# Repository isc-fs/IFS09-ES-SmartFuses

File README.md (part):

# IFS09-ES-SmartFuses

Hardware design, KiCad schematics, PCB layout, multi-rail DC-DC power conversion, and CAN telemetry firmware for the **Smart Fusibles Board** of the **IFS09**, developed for the **ISC Formula Student Racing Team** (Season 2026/2027).

[-green.svg)]()
[-purple.svg)]()
[-red.svg)]()

---

## Getting started

1. Create a GitHub account if you don't have one yet.
2. Download and install [GitHub Desktop](https://desktop.github.com/) (beginner) or [Git CLI](https://git-scm.com/book/en/v2/Getting-Started-Installing-Git) (advanced).
   - If this is your first time using GitHub Desktop, make sure to read the [User Manual](https://help.github.com/desktop/guides/).
   - If this is your first time using Git, start with a tutorial:
     - [Git Tutorial](https://git-scm.com/docs/gittutorial)
     - [Atlassian Git Tutorial](https://www.atlassian.com/git/tutorials/)
   - Keep a copy of [GitHub's Git Cheat Sheet](https://services.github.com/kit/downloads/github-git-cheat-sheet.pdf) handy as a reference.

3. Clone this repository to your machine:
   - **SSH:** `git@github.com:isc-fs/IFS09-ES-SmartFuses.git`
   - **HTTPS:** `https://github.com/isc-fs/IFS09-ES-SmartFuses.git`

---

## How we work with this repository

### Main branches

The repository follows standard ISC branching rules:

* **`main`** is the production branch. It contains only validated hardware releases, schematics, and documentation ready for track operations. Never work directly on it.
* **`dev`** (or active feature branches) is the development and integration point. Never commit directly to `main` — all changes arrive through a reviewed Pull Request.

```
main  ──────────────────●──────────────────────●──▶  (validated releases only)
                        ↑                      ↑
dev   ──────●───●───●───●───●───●───●───●───●──●──▶  (continuous integration)
            ↑   ↑       ↑   ↑   ↑       ↑   ↑
          feat/1 fix/1 feat/2 fix/2   feat/3 fix/3
```

### Feature branches

All work — whether a new hardware revision, firmware update, or bug fix — is done on a **feature branch** created from `dev` (or `main`). When the work is ready, a Pull Request is opened, reviewed, merged, and the branch is deleted.

```
feat/<n>   →  new functionality / hardware addition (feat/1, feat/2, feat/3 ...)
fix/<n>    →  bug fix / schematic correction       (fix/1,  fix/2,  fix/3  ...)
```

### Step-by-step workflow

1. **Create the branch:**
   ```bash
   git checkout main
   git pull origin main
   git checkout -b feat/your-feature-name
   ```
2. **Work and commit:**
   ```bash
   git add .
   git commit -m "feat(hw): add reverse polarity protection to 24V input"
   ```
3. **Push and open Pull Request:**
   ```bash
   git push origin feat/your-feature-name
   ```
   Open a PR against `main` (or `dev`), verify 0 KiCad DRC/ERC errors, provide test evidence, and request review from the Electronics Subsystem Technical Director.

---

## 1. Project Overview & System Purpose

The **IFS09 Smart Fusibles Board** acts as the primary low-voltage (LV) power distribution, multi-rail DC-DC conversion, circuit protection, and digital power telemetry hub for the IFS09 race car.

It evolves the previous passive revision (`PCB_FUSIBLES_XT60` v2) into an active, intelligent subsystem that:
1. Replaces non-locking friction-fit XT-60 connectors with an automotive positive-locking **Molex Mega-Fit** 4-pin header.
2. Protects **12 independent power channels** using **Keystone 3568** automotive mini blade fuse clips with dual-tier blown-fuse detection (instant visual hardware LEDs + CAN telemetry flags).
3. Monitors real-time voltage, current, and power on every branch via **12 Texas Instruments INA260AIPWR** sensors residing on a single shared 400 kHz I2C bus via unique hardware addressing (`0x40` to `0x4B`).
4. Generates onboard regulated power rails directly from the 24V battery: **3.3V logic**, **12V @ 2A** (DTI Inverter logic & motor duo), **12V @ 10W** (isolated Driverless Optical LiDAR), and **19V @ 90W** (LattePanda Mission Computer).
5. Transmits live telemetry to the vehicle ECU and ground station at 50 Hz / 10 Hz over CAN using conflict-free message IDs **`0x380`–`0x383`**.

```
+-----------------------------------------------------------------------------------------+
|                 24V ACCUMULATOR INPUT (Molex Mega-Fit 4-Pin Header, Positive Latch)      |
|                     [ Pin 1,2: +24V_IN (46A max)  |  Pin 3,4: POWER_GND ]                |
+--------------------------------------------+--------------------------------------------+
                                             |
                                             v
                     +------------------------------------------------+
                     | TVS Clamping (SMCJ33A) & Reverse Polarity Prot |
                     +-----------------------+------------------------+
                                             |
        +------------------------------------+------------------------------------+
        |                                                                         |
        v [Direct 24V Fused Bus]                                                  v [DC-DC Power Conversion]
  +-----------+-----------+-----------+                                     +-----------+-----------+-----------+
  | CH 04-07  | CH 08-10  | CH 11-12  |                                     | 3.3V Logic| 12V 2A DTI| 12V 10W   | 19V 90W   |
  | ECU, DASH | REFRI, ACU| AUX, SPARE|                                     | OKI-78SR  | K7812/LMR | OKI-78SR  | LM5145    |
  | SDC, TSAL | DV ACTUAT |           |                                     | 1.5A Max  | 24W Cont. | LiDAR Isol| LattePanda|
  +-----+-----+-----+-----+-----+-----+                                     +-----+-----+-----+-----+-----+-----+-----+---+\
        |           |           |                                                 |           |           |           |
        |           |           |                                                 v           |           |           |
        |           |           |                                            [STM32L431 &]    v           v           v
        |           |           |                                            [TCAN1042V  ]  CH 01       CH 02       CH 03
        |           |           |                                                           (DTI Logic) (LiDAR)   (LattePanda)
        |           |           |                                                             |           |           |
        v           v           v                                                             v           v           v
+-------+-----------+-----------+-------------------------------------------------------------+-----------+-----------+---+
|                    12x AUTOMOTIVE MINI BLADE FUSES (Keystone 3568 Sockets + Blown Fuse LEDs)                    |
+-------+-----------+-----------+-------------------------------------------------------------+-----------+-----------+---+
        |           |           |                                                             |           |           |
        v           v           v                                                             v           v           v
+-------+-----------+-----------+-------------------------------------------------------------+-----------+-----------+---+
|                   12x TI INA260AIPWR DIGITAL POWER SENSORS (Single Shared I2C Bus @ 400 kHz)                    |
|                              Addresses 0x40 to 0x4B (Pin-Strapped via A0 / A1)                                  |
+--------------------------------------------+--------------------------------------------------------------------+
                                             | I2C1 (SCL, SDA) + ALERT Interrupt
                                             v
                     +------------------------------------------------+
                     |       STM32L431CBT6 MCU (ARM Cortex-M4)        |
                     |   Reads 12x INA260, Packets CAN Frames         |
                     +-----------------------+------------------------+
                                             | bxCAN
                                             v
                     +------------------------------------------------+
                     |    TI TCAN1042V-Q1 Transceiver + TVS + Term    |
                     +-----------------------+------------------------+
                                             | CAN_H / CAN_L (500 kbps, IDs 0x380 - 0x383)
                                             v
+-----------------------------------------------------------------------------------------------------------------+
|                        TE CONNECTIVITY AMPSEAL CONNECTOR (Vehicle Output Interface)                             |
|                            Builds directly upon last year's pinout (PCB_FUSIBLES_XT60)                          |
+-----------------------------------------------------------------------------------------------------------------+
```

---

## 2. Hardware Architecture & Electrical Specifications

### 2.1 12 Protected Fused Power Channels
All 12 channels utilize **Keystone 3568** through-hole automotive mini blade fuse clip pairs.

| Ch # | Channel Net | Voltage Domain | Continuous / Peak | Fuse Rating | INA Addr | Primary Connected Subsystem |
| :---: | :--- | :---: | :---: | :---: | :---: | :--- |
| **01** | `12V_DTI_LOGIC` | 12V Regulated | 2.0 A / 3.0 A | 5A | `0x40` | DTI Inverter Logic & Motor Duo Control |
| **02** | `12V_LIDAR` | 12V Regulated | 0.83 A / 1.5 A | 3A | `0x41` | Driverless Optical LiDAR Sensor (10W Isolated) |
| **03** | `19V_LATTEPANDA` | 19V Regulated | 4.74 A / 6.0 A | 10A | `0x42` | LattePanda Mission Computer (90W Continuous) |
| **04** | `24V_ECU` | 24V Raw Bus | 2.0 A / 4.0 A | 5A | `0x43` | Main Vehicle Control Unit (IFS08-CE-ECU) |
| **05** | `24V_DASH_PDU` | 24V Raw Bus | 2.0 A / 4.0 A | 5A | `0x44` | Cockpit Dashboard Displays & PDU Distribution |
| **06** | `24V_SDC` | 24V Raw Bus | 1.5 A / 3.0 A | 5A | `0x45` | Vehicle Shutdown Circuit (SDC Master Loop) |
| **07** | `24V_TSAL` | 24V Raw Bus | 1.5 A / 3.5 A | 5A | `0x46` | Tractive System Active Light Controller |
| **08** | `24V_REFRI` | 24V Raw Bus | 8.0 A / 12.0 A | 15A | `0x47` | Radiator Cooling Fans & Water Pump Motors |
| **09** | `24V_ACU_BMS` | 24V Raw Bus | 2.0 A / 4.0 A | 5A | `0x48` | Accumulator Control Unit & High-Voltage BMS |
| **10** | `24V_DV_ACT` | 24V Raw Bus | 6.0 A / 10.0 A | 15A | `0x49` | Driverless Steering Actuator & Emergency Brake |
| **11** | `24V_AUX_TEL` | 24V Raw Bus | 2.0 A / 4.0 A | 5A | `0x4A` | Telemetry Ground Link Radio, GPS & IMU |
| **12** | `24V_SPARE` | 24V Raw Bus | 2.0 A / 4.0 A | 5A | `0x4B` | Configurable Auxiliary Expansion Rail |

* **Dual-Tier Blown-Fuse Detection:**
  1. *Hardware Visual Tier:* Reverse-biased red 0805 SMD LED in series with a 4.7 kΩ 1/4W resistor across each fuse clip. Normally shorted by the fuse (OFF); turns ON immediately when the fuse blows.
  2. *Software Telemetry Tier:* Downstream INA260 registers bus voltage drop to 0V while raw 24V bus remains active, setting the channel bit in the `SFUS_Fuse_Status_Word` over CAN within 20 ms.

### 2.2 Digital Power Telemetry: 12x TI INA260AIPWR
* **Integrated Precision Shunt:** Built-in 2.0 mΩ (0.1% tolerance, 15 ppm/°C) shunt resistor eliminates 12 large 2512 SMD power resistors and Kelvin sensing routing errors.
* **Single Shared I2C Bus:** Pins `A0` and `A1` are pin-strapped to GND, 3.3V, SDA, or SCL to configure 12 unique 7-bit addresses (`0x40` to `0x4B`), allowing all 12 devices to share `I2C1` with zero multiplexers.
* **36V Common-Mode Margin:** Rated for 0V to 36V continuous (40V abs max), safely withstanding 24V automotive inductive spikes and load dumps.

### 2.3 Integrated Multi-Rail DC-DC Power Conversion
* **3.3V Logic Rail:** Murata **OKI-78SR-3.3/1.5-W36-C** (SIP-3, 36V in, 1.5A out, >85% eff.) supplying STM32L4, TCAN1042V $V_{IO}$, and INA logic.
* **12V @ 2A (24W) - DTI Inverter & Motor Duo:** Mornsun **K7812-2000R3** (SIP-3 module) or TI **LMR33630** (36V, 3A sync buck IC). Output ripple < 40 mVp-p.
* **12V @ 10W (0.83A) - Driverless LiDAR:** Murata **OKI-78SR-12/1.0-W36-C** (SIP-3 module), completely isolating optical LiDAR from motor actuator switching noise.
* **19V @ 90W (4.74A) - LattePanda Mission Computer:** High-efficiency synchronous step-down converter based on the **TI LM5145RGYR** controller with dual **TI CSD18534Q5A** 60V 7.8 mΩ MOSFETs and a 6.8 µH 10A inductor (or high-density industrial 100W PoL module like Cincon EC7BW18-72S19).

### 2.4 Automotive Locking Input: Molex Mega-Fit
* **Part Number:** Molex **172065-0004** (Vertical Header, 4 circuits, 5.70 mm pitch) with positive locking latch and terminal position assurance (TPA).
* **Current Rating:** 23.0 A per terminal. With dual-pin paralleling (Pins 1–2 for `+24V_IN`, Pins 3–4 for `POWER_GND`), the aggregate continuous capacity is **46.0 A**.

### 2.5 Vehicle Output Interface: TE Connectivity AMPSEAL
> [!IMPORTANT]
> **Harness Backwards Compatibility & Dual Keyed Connectors:**  
> To prevent crimping and wiring errors during track assembly, the vehicle output interface splits the 35-pin harness into **two robust, keyed TE AMPSEAL headers**:
> * **`J1` (TE Connectivity 1-776087-1):** 23-pin Horizontal Header dedicated to primary vehicle distribution branches and ground returns.
> * **`J4` (TE Connectivity 776267-1):** 14-pin Horizontal Header dedicated to regulated converter outputs (12V, 19V), CAN bus (`CAN_H`, `CAN_L`), and sensor telemetry channels.
> All proven vehicle branch assignments (ECU, SDC, TSAL, DASH, PDU, REFRI/Cooling, and ACU/BMS) are preserved for harness backwards compatibility.

---

## 3. PCB Layout, Mechanical & Copper Plane Architecture

<p align="center">
  
  &nbsp;&nbsp;&nbsp;&nbsp;
  
</p>

### 3.1 2-Layer Stackup & Copper Plane Strategy
* **Board Dimensions:** **170.0 mm × 85.0 mm** with rounded corners.
* **Layer Count:** Strictly specified as a **TWO-LAYER (2-Layer)** FR4 board ($T_g \ge 150^\circ\text{C}$).
* **Copper Weight:** **2 oz (70 µm finished) copper on both Top and Bottom layers**. Total thickness: 1.6 mm.
* **Bottom Layer (Full-Board GND Plane):**
  - Configured as an unbroken, continuous solid ground (GND) reference plane covering the entire board.
  - Ground pins (Pins 3 & 4) of the Molex Mega-Fit connector pour directly into this plane.
  - High-density thermal/ground via stitching provides an ultra-low impedance return path for high-current motor/fan loads while shielding sensitive digital lines (I2C, CAN, SWD).
* **Top Layer (+24V Supply Bus Plane):**
  - Features a dedicated, low-impedance +24V supply copper plane zone that pours directly from the Mega-Fit input terminals through the TVS/protection stage.
  - Runs across the board to make direct solid contact with the line-side terminals of all 12 Keystone 3568 mini blade fuseholders, functioning as an integrated PCB busbar that eliminates trace necking and minimizes $IR$ drop under 40A+ aggregate vehicle loads.
* **Mechanical Mounting:** Four (4) symmetric **M3 mounting holes** (3.20 mm drill diameter, 6.00 mm outer plated annular ring) placed 5.0 mm from PCB corners.

---

## 4. CAN Telemetry Data Dictionary & ECU Compatibility

The STM32L4 samples all 12 INA260 channels via DMA and broadcasts telemetry frames over the vehicle CAN bus at 500 kbps (Intel Little-Endian format).

> [!NOTE]
> **ECU CAN Compatibility Audit:**  
> The initially evaluated CAN ID `0x4A0` (decimal 1184) collided directly with `AMS_status` in `ecu.dbc`, which is actively decoded by the ECU's `can_rx_task.cpp` for battery safety. The IDs are formally assigned to the **`0x380`–`0x383`** block (decimal 896–899), which is 100% free across all three ECU CAN buses (`FDCAN1` Inverter, `FDCAN2` ACU/Telemetry, `FDCAN3` Dashboard) and grants higher arbitration priority for critical blown-fuse alerts.

| CAN ID | Message Name | Cycle Rate | DLC | Contained Telemetry Signals |
| :---: | :--- | :---: | :---: | :--- |
| **0x380 (896)** | `SFUS_STATUS_SUMMARY` | 50 Hz (20 ms) | 8 | V_Bat_Raw (0.01V), I_Total (0.05A), Fuse_Status_Word (12-bit mask), PCB_Temp (°C), Heartbeat Counter |
| **0x381 (897)** | `SFUS_REGULATED_RAILS` | 10 Hz (100 ms) | 8 | I_DTI_Inv (1mA), I_LiDAR (1mA), I_LattePanda (2mA), V_LattePanda (0.1V), DC-DC Health Bitmask |
| **0x382 (898)** | `SFUS_CRITICAL_RAILS` | 10 Hz (100 ms) | 8 | I_ECU (1mA), I_Dash_PDU (1mA), I_SDC_Loop (1mA), I_TSAL (1mA) |
| **0x383 (899)** | `SFUS_HIGH_POWER_RAILS` | 10 Hz (100 ms) | 8 | I_Refri_Fans (10mA), I_ACU_BMS (1mA), I_DV_Actuators (5mA), I_Aux_Telemetry (1mA) |

---

## 5. Formal Design Documents & Reports

The project specification and verification criteria are documented across the following official engineering artifacts:

| Document | File Link | Description | Status |
| :--- | :--- | :--- | :--- |
| **Schematics Sheet** | [📄 Schematics-2.0.pdf](Schematics-2.0.pdf) | Complete KiCad schematic export with multi-rail DC-DC stages, telemetry, and protection networks. | **v2.0 (Final)** |
| **Work Order (PDF)** | [📄 WO_ES-IFS09-SmartFuses.pdf](WO_ES-IFS09-SmartFuses.pdf) | Formal published Work Order specification generated using the official ISC team base template (`IFS_09_W_Template_Base_CB.docx`). | **Rev 1.0 (Released)** |
| **Work Order (DOCX)** | [📄 WO_ES-IFS09-SmartFuses.docx](WO_ES-IFS09-SmartFuses.docx) | Microsoft Word source document with native Jost / IBM Plex Sans typography, cover page, and ISC table styles. | **Rev 1.0 (Released)** |
| **CAN Database** | [📄 SMART_FUSIBLES.dbc](docs/dbc/SMART_FUSIBLES.dbc) | Vector CAN database defining messages `0x380`–`0x383` ready for ECU integration and CANoe/PCAN logging. | **v1.0 (Active)** |
| **Markdown Specification** | [📄 WORK_ORDER_SMART_FUSIBLES.md](docs/WORK_ORDER_SMART_FUSIBLES.md) | Synchronized Markdown specification for Git version control and quick online reference. | **Rev 1.0** |

---

## 6. Repository Structure

```
IFS09-ES-SmartFuses/
├── docs/                              # Documentation & Database Assets
│   ├── dbc/
│   │   └── SMART_FUSIBLES.dbc         # Official Vector CAN DBC File
│   ├── images/                        # PCB Layout & 3D Render Graphics
│   │   ├── pcb_layout_2d.png          # 2D PCB Layout Routing View (170x85mm)
│   │   └── pcb_render_3d.png          # 3D Populated PCB Render Model
│   ├── SCHEMATIC_AUDIT_REPORT.md      # Electrical & Design Integrity Audit
│   └── WORK_ORDER_SMART_FUSIBLES.md   # Synchronized Markdown Specification
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
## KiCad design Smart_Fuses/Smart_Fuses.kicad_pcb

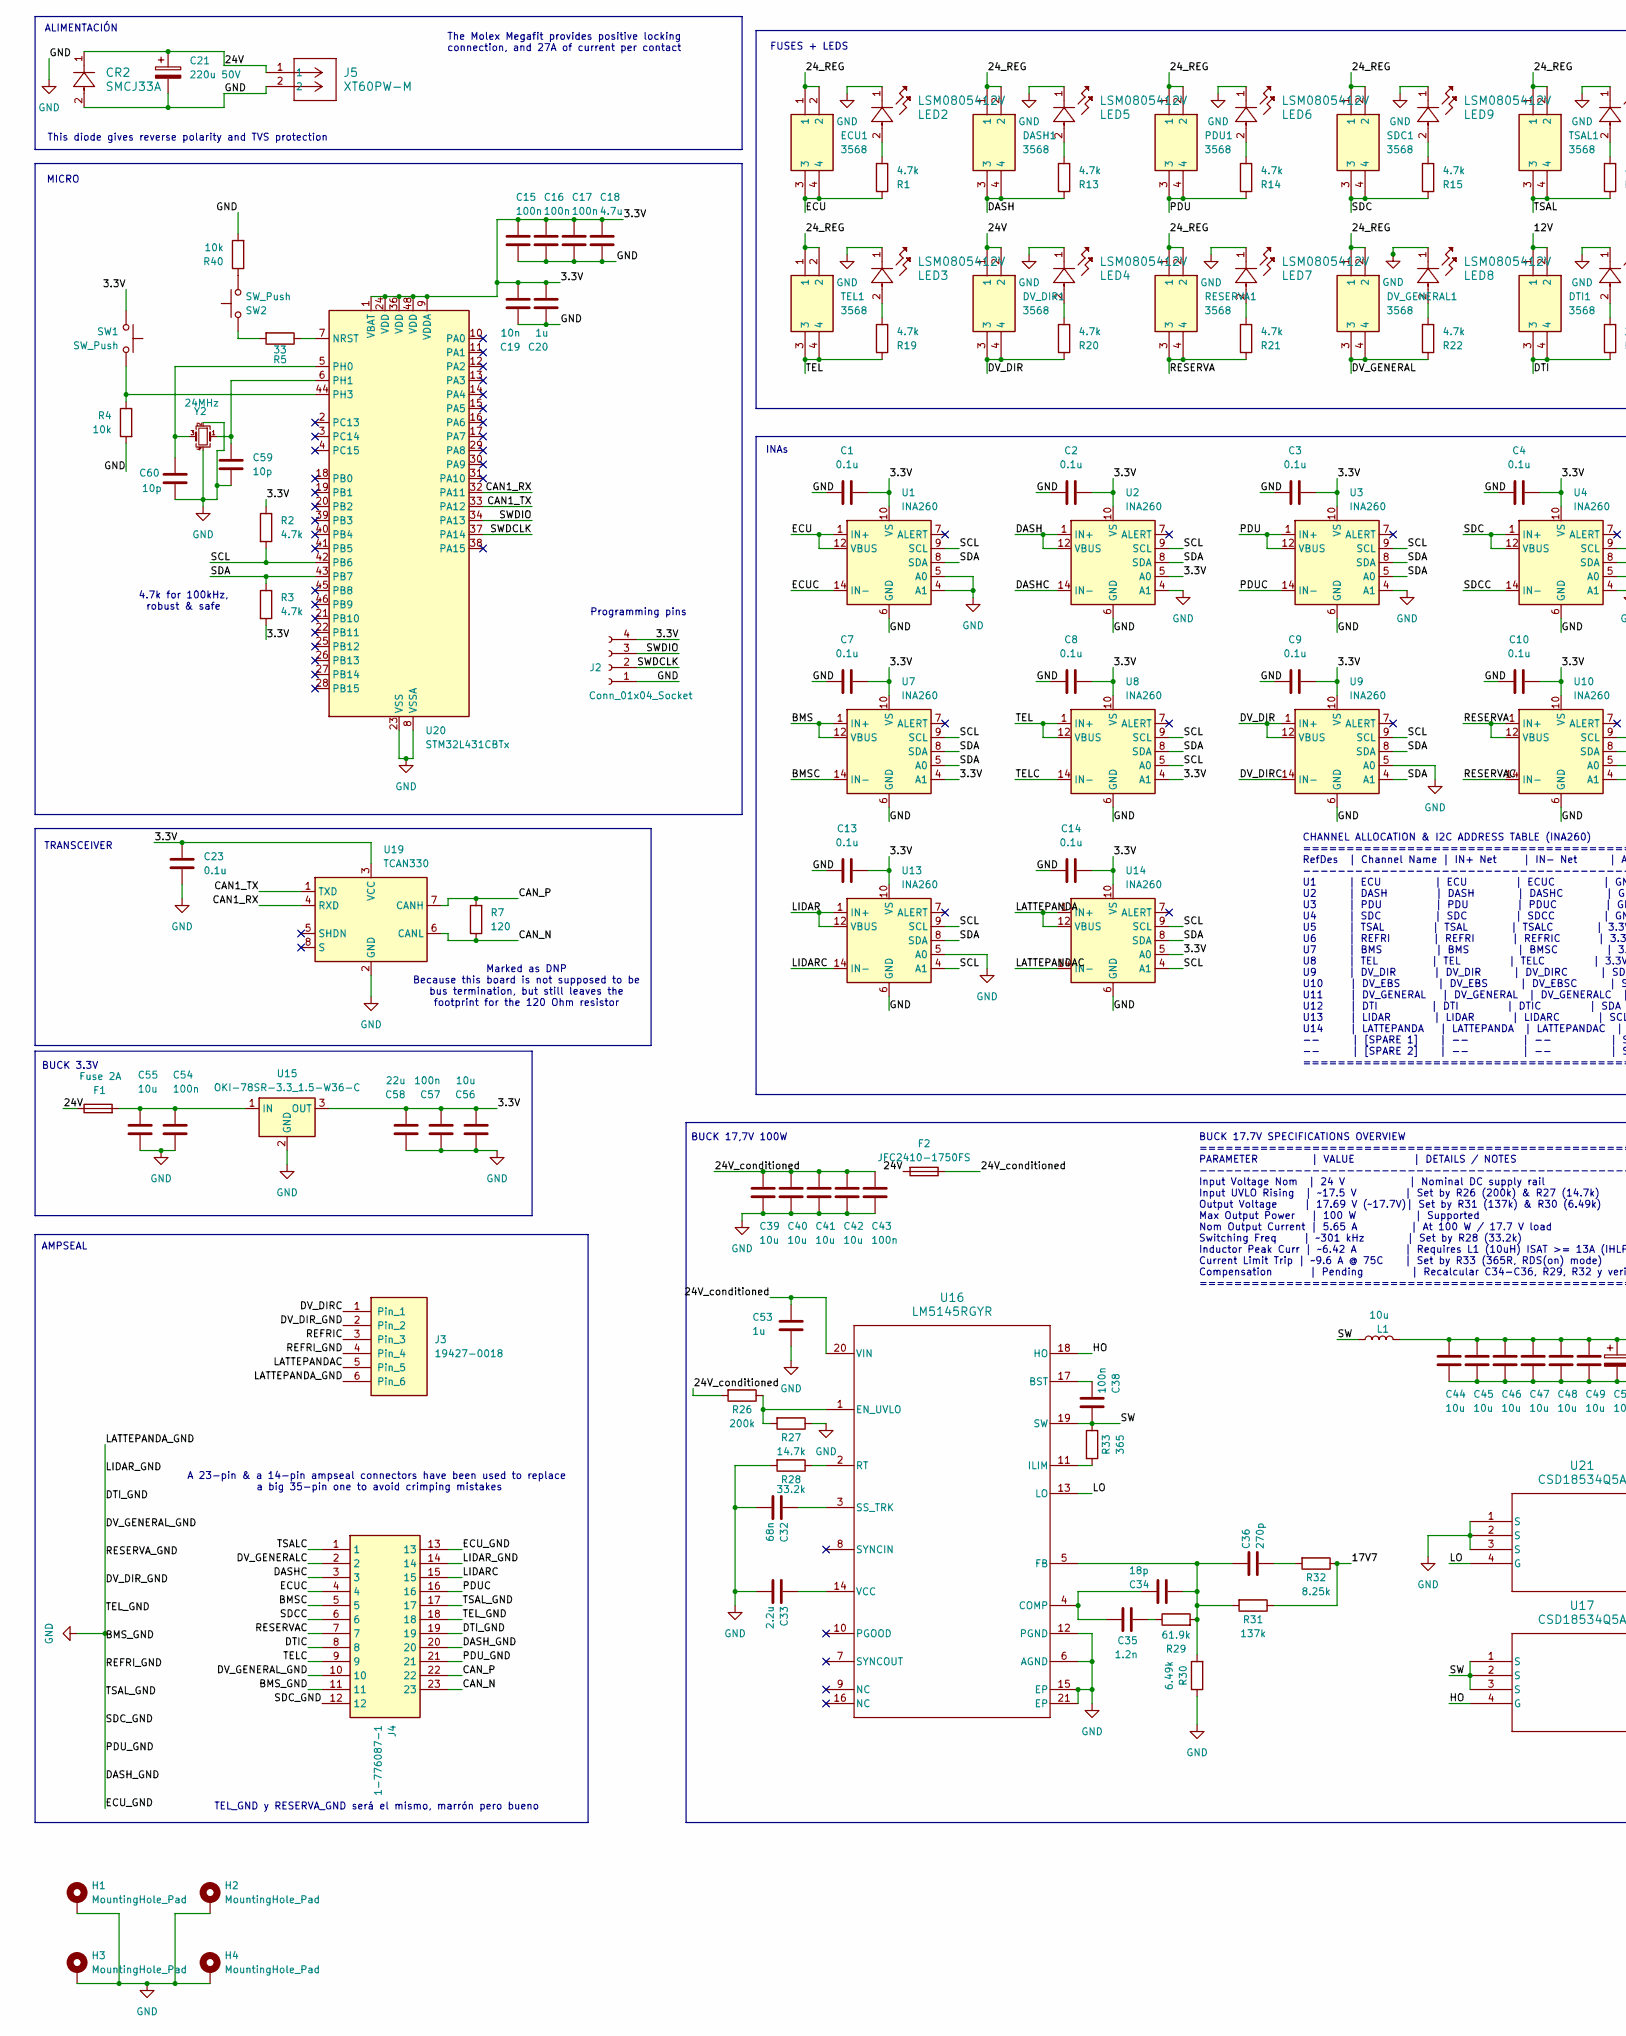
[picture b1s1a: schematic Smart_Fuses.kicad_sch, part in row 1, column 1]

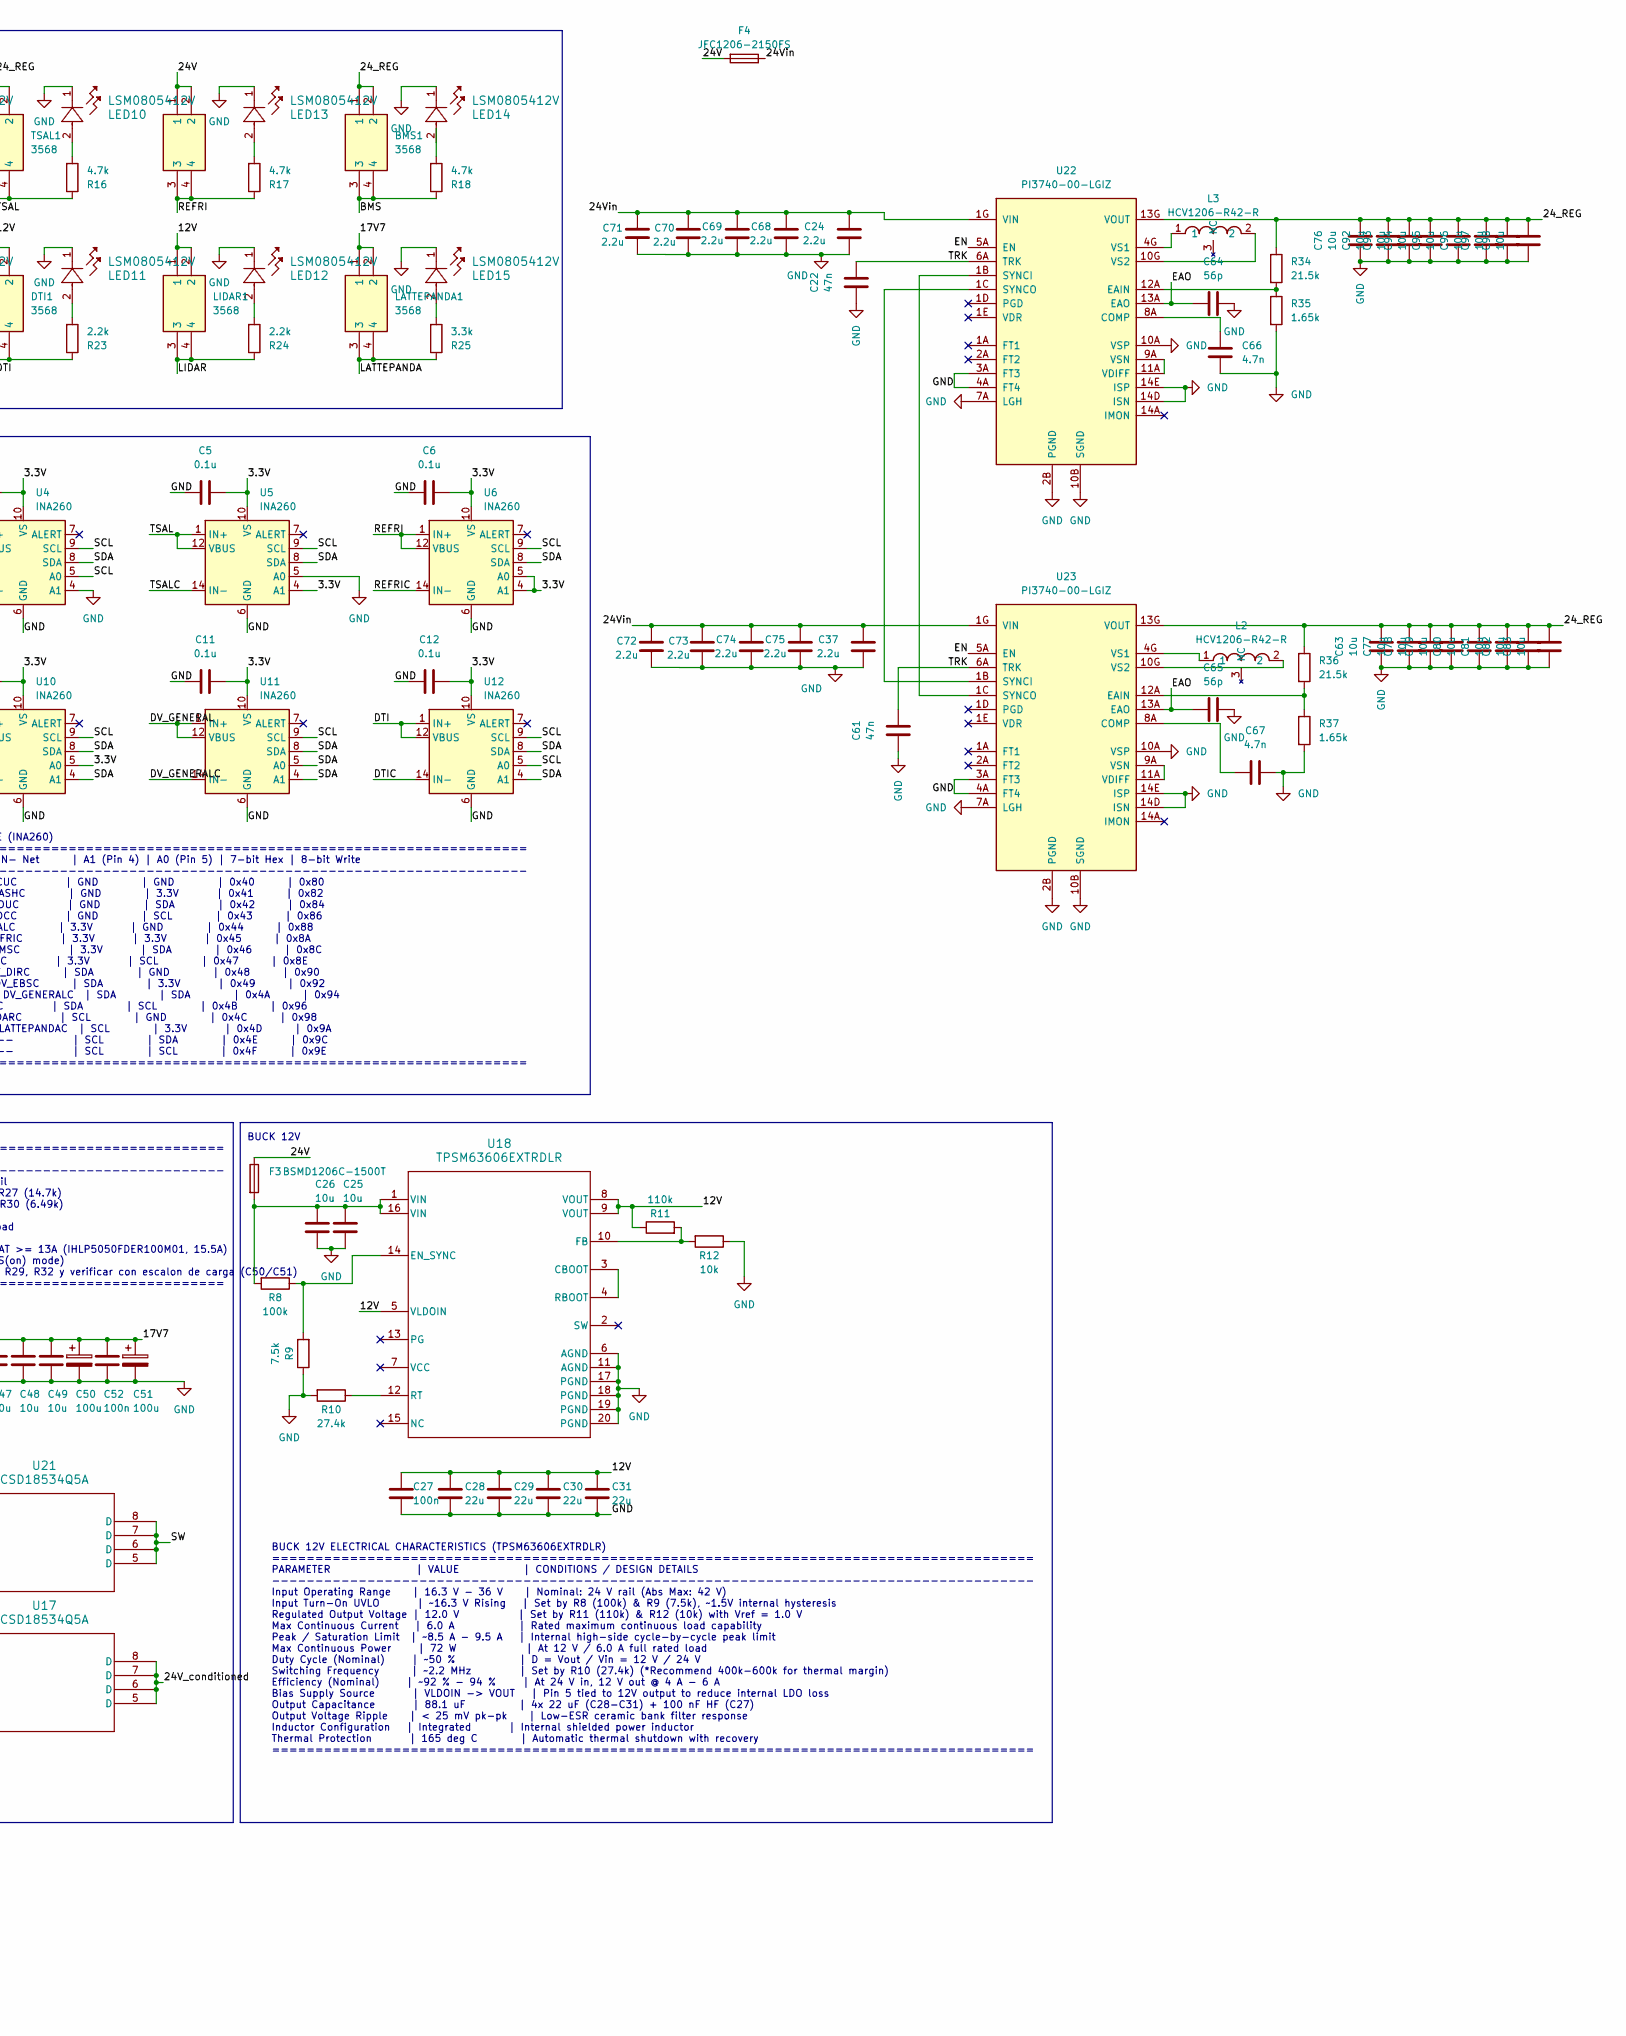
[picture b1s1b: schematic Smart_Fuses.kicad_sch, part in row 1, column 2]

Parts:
BMS1: 3568; Mouser Part Number 534-3568
C1, C2, C3, C4, C5, C6, C7, C8, C9, C10, C11, C12, C13, C14, C23: 0.1u; C_0805_2012Metric_Pad1.18x1.45mm_HandSolder
C15, C16, C17: 100n; C_0603_1608Metric
C18: 4.7u; C_0603_1608Metric
C19: 10n; C_0603_1608Metric
C20: 1u; C_0603_1608Metric
C21: 220u 50V; CP_Elec_10x10.2
C22, C61: 47n; C_0603_1608Metric
C24, C37, C68, C69, C70, C71, C72, C73, C74, C75: 2.2u; C_1210_3225Metric
C25, C26, C39, C40, C41, C42, C44, C45, C46, C47, C48, C49, C55: 10u; C_1206_3216Metric; MPN GRT31CR6YA106KE01L
C27, C38, C43, C52, C54, C57: 100n; C_0805_2012Metric_Pad1.18x1.45mm_HandSolder
C28, C29, C30, C31: 22u; C_1210_3225Metric; MPN GMK325BJ226MM-P
C32: 68n; C_0805_2012Metric_Pad1.18x1.45mm_HandSolder
C33: 2.2u; C_0805_2012Metric_Pad1.18x1.45mm_HandSolder
C34: 18p; C_0805_2012Metric_Pad1.18x1.45mm_HandSolder
C35: 1.2n; C_0805_2012Metric_Pad1.18x1.45mm_HandSolder
C36: 270p; C_0805_2012Metric_Pad1.18x1.45mm_HandSolder
C50: 100u; CP_Elec_6.3x7.7; MPN 865080545012
C51: 100u; CP_Elec_6.3x7.7; MPN GRM32ER71H106KA12L
C53: 1u; C_0805_2012Metric_Pad1.18x1.45mm_HandSolder
C56: 10u; C_0805_2012Metric_Pad1.18x1.45mm_HandSolder
C58: 22u; C_0805_2012Metric_Pad1.18x1.45mm_HandSolder
C59, C60: 10p; C_0603_1608Metric_Pad1.08x0.95mm_HandSolder
C63, C76, C77, C78, C79, C80, C81, C82, C83, C92, C93, C94, C95, C96, C97, C98: 10u; C_1210_3225Metric
C64, C65: 56p; C_0603_1608Metric
C66, C67: 4.7n; C_0603_1608Metric
CR2: SMCJ33A; D_SMC
DASH1: 3568; Mouser Part Number 534-3568
DTI1: 3568; Mouser Part Number 534-3568
DV_DIR1: 3568; Mouser Part Number 534-3568
DV_GENERAL1: 3568; Mouser Part Number 534-3568
ECU1: 3568; Mouser Part Number 534-3568
F1: Fuse 2A; Fuse_1206_3216Metric
F2: JFC2410-1750FS; Fuse_2410_6125Metric_JFC2410
F3: BSMD1206C-1500T; Fuse_1206_3216Metric
F4: JFC1206-2150FS; Fuse_1206_3216Metric
H1, H2, H3, H4: MountingHole_Pad; MountingHole_3.2mm_M3_DIN965_Pad
J2: Conn_01x04_Socket; PinHeader_1x04_P2.54mm_Vertical
J3: 19427-0018; Molex_MX150L_19427-0018_2x03_P5.84mm_Horizontal
J4: 1-776087-1; 17760871; Mouser Part Number 571-1-776087-1
J5: XT60PW-M; CONN_XT60PW-M_AMA
L1: 10u; L_Vishay_IHLP-5050
L2, L3: HCV1206-R42-R; L_Eaton_HCV1206-R42-R
LATTEPANDA1: 3568; Mouser Part Number 534-3568
LED2, LED3, LED4, LED5, LED6, LED7, LED8, LED9, LED10, LED11, LED12, LED13, LED14, LED15: LSM0805412V; LED_LSM0805-2P0X1P25X0P8_VCC
LIDAR1: 3568; Mouser Part Number 534-3568
PDU1: 3568; Mouser Part Number 534-3568
R1, R13, R14, R15, R16, R17, R18, R19, R20, R21, R22: 4.7k; R_1206_3216Metric_Pad1.30x1.75mm_HandSolder
R2, R3: 4.7k; R_0603_1608Metric
R4, R12, R40: 10k; R_0603_1608Metric
R5: 33; R_0603_1608Metric
R7: 120; R_0603_1608Metric
R8: 100k; R_0603_1608Metric
R9: 7.5k; R_0603_1608Metric
R10: 27.4k; R_0603_1608Metric
R11: 110k; R_0603_1608Metric
R23, R24: 2.2k; R_1206_3216Metric_Pad1.30x1.75mm_HandSolder
R25: 3.3k; R_1206_3216Metric_Pad1.30x1.75mm_HandSolder
R26: 200k; R_0603_1608Metric
R27: 14.7k; R_0603_1608Metric
R28: 33.2k; R_0603_1608Metric
R29: 61.9k; R_0603_1608Metric
R30: 6.49k; R_0603_1608Metric
R31: 137k; R_0603_1608Metric
R32: 8.25k; R_0603_1608Metric
R33: 365; R_0603_1608Metric
R34, R36: 21.5k; R_0603_1608Metric
R35, R37: 1.65k; R_0603_1608Metric
REFRI1: 3568; Mouser Part Number 534-3568
RESERVA1: 3568; Mouser Part Number 534-3568
SDC1: 3568; Mouser Part Number 534-3568
SW1, SW2: SW_Push; SW_SPST_B3U-1000P-B
TEL1: 3568; Mouser Part Number 534-3568
TSAL1: 3568; Mouser Part Number 534-3568
U1, U2, U3, U4, U5, U6, U7, U8, U9, U10, U11, U12, U13, U14: INA260; TSSOP-16_4.4x5mm_P0.65mm
U15: OKI-78SR-3.3_1.5-W36-C; Converter_DCDC_Murata_OKI-78SR_Vertical
U16: LM5145RGYR; RGY0020B
U17, U21: CSD18534Q5A; PowerPAK_SO-8_Single
U18: TPSM63606EXTRDLR; RDL0020A-MFG
U19: TCAN330; SOIC-8_3.9x4.9mm_P1.27mm
U20: STM32L431CBTx; LQFP-48_7x7mm_P0.5mm
U22, U23: PI3740-00-LGIZ; Vicor_PI3740-00-LGIZ_LGA-108_10x14mm
Y2: 24MHz; Crystal_SMD_2520-4Pin_2.5x2.0mm

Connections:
/3.3V: C1.2, C2.2, C3.2, C4.2, C5.2, C6.2, C7.2, C8.2, C9.2, C10.2, C11.2, C12.2, C13.2, C14.2, C15.1, C16.1, C17.1, C18.1, C19.2, C20.2, C23.1, C56.1, C57.1, C58.1, J2.4, R2.1, R3.2, SW1.2, U1.10 (VS), U2.5 (A0), U2.10 (VS), U3.10 (VS), U4.10 (VS), U5.4 (A1), U5.10 (VS), U6.4 (A1), U6.5 (A0), U6.10 (VS), U7.4 (A1), U7.10 (VS), U8.4 (A1), U8.10 (VS), U9.10 (VS), U10.5 (A0), U10.10 (VS), U11.10 (VS), U12.10 (VS), U13.10 (VS), U14.5 (A0), U14.10 (VS), U15.3 (OUT), U19.3 (VCC), U20.1 (VBAT), U20.9 (VDDA), U20.24 (VDD), U20.36 (VDD), U20.48 (VDD)
/12V: C27.1, C28.1, C29.1, C30.1, C31.1, DTI1.1, DTI1.2, LIDAR1.1, LIDAR1.2, R11.1, U18.5 (VLDOIN), U18.8 (VOUT), U18.9 (VOUT)
/17V7: C44.1, C45.1, C46.1, C47.1, C48.1, C49.1, C50.1, C51.1, C52.1, L1.2, LATTEPANDA1.1, LATTEPANDA1.2, R31.1, R32.1
/24V: C21.1, CR2.1, DV_DIR1.1, DV_DIR1.2, F1.1, F2.1, F3.2, F4.1, J5.1, REFRI1.1, REFRI1.2
/24V_conditioned: C39.1, C40.1, C41.1, C42.1, C43.1, C53.2, F2.2, R26.2, U16.20 (VIN), U17.5 (D), U17.6 (D), U17.7 (D), U17.8 (D)
/24_REG: BMS1.1, BMS1.2, C63.2, C76.2, C77.2, C78.2, C79.2, C80.2, C81.2, C82.2, C83.2, C92.2, C93.2, C94.2, C95.2, C96.2, C97.2, C98.2, DASH1.1, DASH1.2, DV_GENERAL1.1, DV_GENERAL1.2, ECU1.1, ECU1.2, PDU1.1, PDU1.2, R34.1, R36.1, RESERVA1.1, RESERVA1.2, SDC1.1, SDC1.2, TEL1.1, TEL1.2, TSAL1.1, TSAL1.2, U22.13G (VOUT), U22.13H (VOUT), U22.13J (VOUT), U22.13K (VOUT), U22.14G (VOUT), U22.14H (VOUT), U22.14J (VOUT), U22.14K (VOUT), U23.13G (VOUT), U23.13H (VOUT), U23.13J (VOUT), U23.13K (VOUT), U23.14G (VOUT), U23.14H (VOUT), U23.14J (VOUT), U23.14K (VOUT)
/BMS: BMS1.3, BMS1.4, R18.1, U7.1 (IN+), U7.2 (IN+), U7.3 (IN+), U7.12 (VBUS)
/BMSC: J4.5, U7.14 (IN-), U7.15 (IN-), U7.16 (IN-)
/CAN1_RX: U19.4 (RXD), U20.32 (PA11)
/CAN1_TX: U19.1 (TXD), U20.33 (PA12)
/CAN_N: J4.23, R7.1, U19.6 (CANL)
/CAN_P: J4.22, R7.2, U19.7 (CANH)
/DASH: DASH1.3, DASH1.4, R13.1, U2.1 (IN+), U2.2 (IN+), U2.3 (IN+), U2.12 (VBUS)
/DASHC: J4.3, U2.14 (IN-), U2.15 (IN-), U2.16 (IN-)
/DTI: DTI1.3, DTI1.4, R23.1, U12.1 (IN+), U12.2 (IN+), U12.3 (IN+), U12.12 (VBUS)
/DTIC: J4.8, U12.14 (IN-), U12.15 (IN-), U12.16 (IN-)
/DV_DIR: DV_DIR1.3, DV_DIR1.4, R20.1, U9.1 (IN+), U9.2 (IN+), U9.3 (IN+), U9.12 (VBUS)
/DV_DIRC: J3.1, U9.14 (IN-), U9.15 (IN-), U9.16 (IN-)
/DV_GENERAL: DV_GENERAL1.3, DV_GENERAL1.4, R22.1, U11.1 (IN+), U11.2 (IN+), U11.3 (IN+), U11.12 (VBUS)
/DV_GENERALC: J4.2, U11.14 (IN-), U11.15 (IN-), U11.16 (IN-)
/EAO: C64.1, C65.1, U22.13A (EAO), U23.13A (EAO)
/ECU: ECU1.3, ECU1.4, R1.1, U1.1 (IN+), U1.2 (IN+), U1.3 (IN+), U1.12 (VBUS)
/ECUC: J4.4, U1.14 (IN-), U1.15 (IN-), U1.16 (IN-)
/EN: U22.5A (EN), U23.5A (EN)
/HO: U16.18 (HO), U17.4 (G)
/LATTEPANDA: LATTEPANDA1.3, LATTEPANDA1.4, R25.1, U14.1 (IN+), U14.2 (IN+), U14.3 (IN+), U14.12 (VBUS)
/LATTEPANDAC: J3.5, U14.14 (IN-), U14.15 (IN-), U14.16 (IN-)
/LIDAR: LIDAR1.3, LIDAR1.4, R24.1, U13.1 (IN+), U13.2 (IN+), U13.3 (IN+), U13.12 (VBUS)
/LIDARC: J4.15, U13.14 (IN-), U13.15 (IN-), U13.16 (IN-)
/LO: U16.13 (LO), U21.4 (G)
/PDU: PDU1.3, PDU1.4, R14.1, U3.1 (IN+), U3.2 (IN+), U3.3 (IN+), U3.12 (VBUS)
/PDUC: J4.16, U3.14 (IN-), U3.15 (IN-), U3.16 (IN-)
/REFRI: R17.1, REFRI1.3, REFRI1.4, U6.1 (IN+), U6.2 (IN+), U6.3 (IN+), U6.12 (VBUS)
/REFRIC: J3.3, U6.14 (IN-), U6.15 (IN-), U6.16 (IN-)
/RESERVA: R21.1, RESERVA1.3, RESERVA1.4, U10.1 (IN+), U10.2 (IN+), U10.3 (IN+), U10.12 (VBUS)
/RESERVAC: J4.7, U10.14 (IN-), U10.15 (IN-), U10.16 (IN-)
/SCL: R2.2, U1.9 (SCL), U2.9 (SCL), U3.9 (SCL), U4.5 (A0), U4.9 (SCL), U5.9 (SCL), U6.9 (SCL), U7.9 (SCL), U8.5 (A0), U8.9 (SCL), U9.9 (SCL), U10.9 (SCL), U11.9 (SCL), U12.5 (A0), U12.9 (SCL), U13.4 (A1), U13.9 (SCL), U14.4 (A1), U14.9 (SCL), U20.42 (PB6)
/SDA: R3.1, U1.8 (SDA), U2.8 (SDA), U3.5 (A0), U3.8 (SDA), U4.8 (SDA), U5.8 (SDA), U6.8 (SDA), U7.5 (A0), U7.8 (SDA), U8.8 (SDA), U9.4 (A1), U9.8 (SDA), U10.4 (A1), U10.8 (SDA), U11.4 (A1), U11.5 (A0), U11.8 (SDA), U12.4 (A1), U12.8 (SDA), U13.8 (SDA), U14.8 (SDA), U20.43 (PB7)
/SDC: R15.1, SDC1.3, SDC1.4, U4.1 (IN+), U4.2 (IN+), U4.3 (IN+), U4.12 (VBUS)
/SDCC: J4.6, U4.14 (IN-), U4.15 (IN-), U4.16 (IN-)
/SW: C38.1, L1.1, R33.1, U16.19 (SW), U17.1 (S), U17.2 (S), U17.3 (S), U21.5 (D), U21.6 (D), U21.7 (D), U21.8 (D)
/SWDCLK: J2.2, U20.37 (PA14)
/SWDIO: J2.3, U20.34 (PA13)
/TEL: R19.1, TEL1.3, TEL1.4, U8.1 (IN+), U8.2 (IN+), U8.3 (IN+), U8.12 (VBUS)
/TELC: J4.9, U8.14 (IN-), U8.15 (IN-), U8.16 (IN-)
/TRK: C22.2, C61.2, U22.6A (TRK), U23.6A (TRK)
/TSAL: R16.1, TSAL1.3, TSAL1.4, U5.1 (IN+), U5.2 (IN+), U5.3 (IN+), U5.12 (VBUS)
/TSALC: J4.1, U5.14 (IN-), U5.15 (IN-), U5.16 (IN-)
GND: C1.1, C2.1, C3.1, C4.1, C5.1, C6.1, C7.1, C8.1, C9.1, C10.1, C11.1, C12.1, C13.1, C14.1, C15.2, C16.2, C17.2, C18.2, C19.1, C20.1, C21.2, C22.1, C23.2, C24.1, C25.2, C26.2, C27.2, C28.2, C29.2, C30.2, C31.2, C32.2, C33.2, C37.1, C39.2, C40.2, C41.2, C42.2, C43.2, C44.2, C45.2, C46.2, C47.2, C48.2, C49.2, C50.2, C51.2, C52.2, C53.1, C54.1, C55.1, C56.2, C57.2, C58.2, C59.2, C60.2, C61.1, C63.1, C64.2, C65.2, C66.2, C67.2, C68.1, C69.1, C70.1, C71.1, C72.1, C73.1, C74.1, C75.1, C76.1, C77.1, C78.1, C79.1, C80.1, C81.1, C82.1, C83.1, C92.1, C93.1, C94.1, C95.1, C96.1, C97.1, C98.1, CR2.2, H1.1 (1_1), H2.1 (1_1), H3.1 (1_1), H4.1 (1_1), J2.1, J3.2, J3.4, J3.6, J4.10, J4.11, J4.12, J4.13, J4.14, J4.17, J4.18, J4.19, J4.20, J4.21, J5.2, LED2.1, LED3.1, LED4.1, LED5.1, LED6.1, LED7.1, LED8.1, LED9.1, LED10.1, LED11.1, LED12.1, LED13.1, LED14.1, LED15.1, R4.2, R9.1, R10.2, R12.1, R27.1, R28.2, R30.1, R35.2, R37.2, R40.2, U1.4 (A1), U1.5 (A0), U1.6 (GND), U1.11 (GND), U2.4 (A1), U2.6 (GND), U2.11 (GND), U3.4 (A1), U3.6 (GND), U3.11 (GND), U4.4 (A1), U4.6 (GND), U4.11 (GND), U5.5 (A0), U5.6 (GND), U5.11 (GND), U6.6 (GND), U6.11 (GND), U7.6 (GND), U7.11 (GND), U8.6 (GND), U8.11 (GND), U9.5 (A0), U9.6 (GND), U9.11 (GND), U10.6 (GND), U10.11 (GND), U11.6 (GND), U11.11 (GND), U12.6 (GND), U12.11 (GND), U13.5 (A0), U13.6 (GND), U13.11 (GND), U14.6 (GND), U14.11 (GND), U15.2 (GND), U16.6 (AGND), U16.12 (PGND), U16.15 (EP), U16.21 (EP), U18.6 (AGND), U18.11 (AGND), U18.17 (PGND), U18.18 (PGND), U18.19 (PGND), U18.20 (PGND), U19.2 (GND), U20.8 (VSSA), U20.23 (VSS), U20.35 (VSS), U20.47 (VSS), U21.1 (S), U21.2 (S), U21.3 (S), U22.2B (PGND), U22.2C (PGND), U22.2D (PGND), U22.2E (PGND), U22.3A (FT3), U22.3B (PGND), U22.3C (PGND), U22.3D (PGND), U22.3E (PGND), U22.4A (FT4), U22.4B (PGND), U22.4C (PGND), U22.4D (PGND), U22.4E (PGND), U22.5B (PGND), U22.5C (PGND), U22.5D (PGND), U22.5E (PGND), U22.6B (PGND), U22.6C (PGND), U22.6D (PGND), U22.6E (PGND), U22.7A (LGH), U22.7B (PGND), U22.7C (PGND), U22.7D (PGND), U22.7E (PGND), U22.7F (PGND), U22.7G (PGND), U22.7H (PGND), U22.7J (PGND), U22.7K (PGND), U22.8B (PGND), U22.8C (PGND), U22.8D (PGND), U22.8E (PGND), U22.8F (PGND), U22.8G (PGND), U22.8H (PGND), U22.8J (PGND), U22.8K (PGND), U22.9B (PGND), U22.9C (PGND), U22.9D (PGND), U22.9E (PGND), U22.10A (VSP), U22.10B (SGND), U22.10C (SGND), U22.10D (SGND), U22.10E (SGND), U22.11B (SGND), U22.11C (SGND), U22.11D (SGND), U22.11E (SGND), U22.12B (SGND), U22.12C (SGND), U22.12D (SGND), U22.12E (SGND), U22.13B (SGND), U22.14B (SGND), U22.14D (ISN), U22.14E (ISP), U23.2B (PGND), U23.2C (PGND), U23.2D (PGND), U23.2E (PGND), U23.3A (FT3), U23.3B (PGND), U23.3C (PGND), U23.3D (PGND), U23.3E (PGND), U23.4A (FT4), U23.4B (PGND), U23.4C (PGND), U23.4D (PGND), U23.4E (PGND), U23.5B (PGND), U23.5C (PGND), U23.5D (PGND), U23.5E (PGND), U23.6B (PGND), U23.6C (PGND), U23.6D (PGND), U23.6E (PGND), U23.7A (LGH), U23.7B (PGND), U23.7C (PGND), U23.7D (PGND), U23.7E (PGND), U23.7F (PGND), U23.7G (PGND), U23.7H (PGND), U23.7J (PGND), U23.7K (PGND), U23.8B (PGND), U23.8C (PGND), U23.8D (PGND), U23.8E (PGND), U23.8F (PGND), U23.8G (PGND), U23.8H (PGND), U23.8J (PGND), U23.8K (PGND), U23.9B (PGND), U23.9C (PGND), U23.9D (PGND), U23.9E (PGND), U23.10A (VSP), U23.10B (SGND), U23.10C (SGND), U23.10D (SGND), U23.10E (SGND), U23.11B (SGND), U23.11C (SGND), U23.11D (SGND), U23.11E (SGND), U23.12B (SGND), U23.12C (SGND), U23.12D (SGND), U23.12E (SGND), U23.13B (SGND), U23.14B (SGND), U23.14D (ISN), U23.14E (ISP), Y2.2, Y2.4
unnamed: C25.1, C26.1, F3.1, R8.2, U18.1 (VIN), U18.16 (VIN)
unnamed: C35.1, R29.1
unnamed: C36.2, R32.2
unnamed: L2.1, U23.4G (VS1), U23.4H (VS1), U23.4J (VS1), U23.4K (VS1), U23.5G (VS1), U23.5H (VS1), U23.5J (VS1), U23.5K (VS1)
unnamed: L2.2, U23.10G (VS2), U23.10H (VS2), U23.10J (VS2), U23.10K (VS2), U23.11G (VS2), U23.11H (VS2), U23.11J (VS2), U23.11K (VS2)
unnamed: L3.1, U22.4G (VS1), U22.4H (VS1), U22.4J (VS1), U22.4K (VS1), U22.5G (VS1), U22.5H (VS1), U22.5J (VS1), U22.5K (VS1)
unnamed: L3.2, U22.10G (VS2), U22.10H (VS2), U22.10J (VS2), U22.10K (VS2), U22.11G (VS2), U22.11H (VS2), U22.11J (VS2), U22.11K (VS2)
unnamed: LED2.2, R1.2
unnamed: LED3.2, R19.2
unnamed: LED4.2, R20.2
unnamed: LED5.2, R13.2
unnamed: LED6.2, R14.2
unnamed: LED7.2, R21.2
unnamed: LED8.2, R22.2
unnamed: LED9.2, R15.2
unnamed: LED10.2, R16.2
unnamed: LED11.2, R23.2
unnamed: LED12.2, R24.2
unnamed: LED13.2, R17.2
unnamed: LED14.2, R18.2
unnamed: LED15.2, R25.2
unnamed: R5.2, SW2.2
unnamed: R40.1, SW2.1
unnamed: C54.2, C55.2, F1.2, U15.1 (IN)
unnamed: C38.2, U16.17 (BST)
unnamed: C34.1, C35.2, U16.4 (COMP)
unnamed: R26.1, R27.2, U16.1 (EN_UVLO)
unnamed: C34.2, C36.1, R29.2, R30.2, R31.2, U16.5 (FB)
unnamed: R33.2, U16.11 (ILIM)
unnamed: R28.1, U16.2 (RT)
unnamed: C32.1, U16.3 (SS_TRK)
unnamed: C33.1, U16.14 (VCC)
unnamed: U18.3 (CBOOT), U18.4 (RBOOT)
unnamed: R8.1, R9.2, U18.14 (EN_SYNC)
unnamed: R11.2, R12.2, U18.10 (FB)
unnamed: R10.1, U18.12 (RT)
unnamed: R5.1, U20.7 (NRST)
unnamed: C60.1, U20.5 (PH0), Y2.3
unnamed: C59.1, U20.6 (PH1), Y2.1
unnamed: R4.1, SW1.1, U20.44 (PH3)
unnamed: C66.1, U22.8A (COMP)
unnamed: R34.2, R35.1, U22.12A (EAIN)
unnamed: U22.1B (SYNCI), U23.1C (SYNCO)
unnamed: U22.1C (SYNCO), U23.1B (SYNCI)
unnamed: U22.9A (VSN), U22.11A (VDIFF)
unnamed: C67.1, U23.8A (COMP)
unnamed: R36.2, R37.1, U23.12A (EAIN)
unnamed: U23.9A (VSN), U23.11A (VDIFF)
VIN: C24.2, C37.2, C68.2, C69.2, C70.2, C71.2, C72.2, C73.2, C74.2, C75.2, F4.2, U22.1G (VIN), U22.1H (VIN), U22.1J (VIN), U22.1K (VIN), U22.2G (VIN), U22.2H (VIN), U22.2J (VIN), U22.2K (VIN), U23.1G (VIN), U23.1H (VIN), U23.1J (VIN), U23.1K (VIN), U23.2G (VIN), U23.2H (VIN), U23.2J (VIN), U23.2K (VIN)

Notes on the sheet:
INAs
A 23-pin & a 14-pin ampseal connectors have been used to replace a big 35-pin one to avoid crimping mistakes
TEL_GND y RESERVA_GND será el mismo, marrón pero bueno
MICRO
4.7k for 100kHz, robust & safe
TRANSCEIVER
BUCK 3.3V
This diode gives reverse polarity and TVS protection
FUSES + LEDS
BUCK 12V
CHANNEL ALLOCATION & I2C ADDRESS TABLE (INA260) ======================================================================================== RefDes | Channel Name | IN+ Net | IN- Net | A1 (Pin 4) | A0 (Pin 5) | 7-bit Hex | 8-bit Write --------------------------------------------------------------------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
BUCK 12V ELECTRICAL CHARACTERISTICS (TPSM63606EXTRDLR) ======================================================================================== PARAMETER | VALUE | CONDITIONS / DESIGN DETAILS ---------------------------------------------------------------------------------------- Input Operating Ra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
AMPSEAL
Marked as DNP Because this board is not supposed to be bus termination, but still leaves the footprint for the 120 Ohm resistor
The Molex Megafit provides positive locking connection, and 27A of current per contact
Programming pins
BUCK 17,7V 100W
BUCK 17.7V SPECIFICATIONS OVERVIEW ================================================================= PARAMETER | VALUE | DETAILS / NOTES ----------------------------------------------------------------- Input Voltage Nom | 24 V | Nominal DC supply rail Input UVLO Rising | ~17.5 V | Set by R26 (200k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
ALIMENTACIÓN

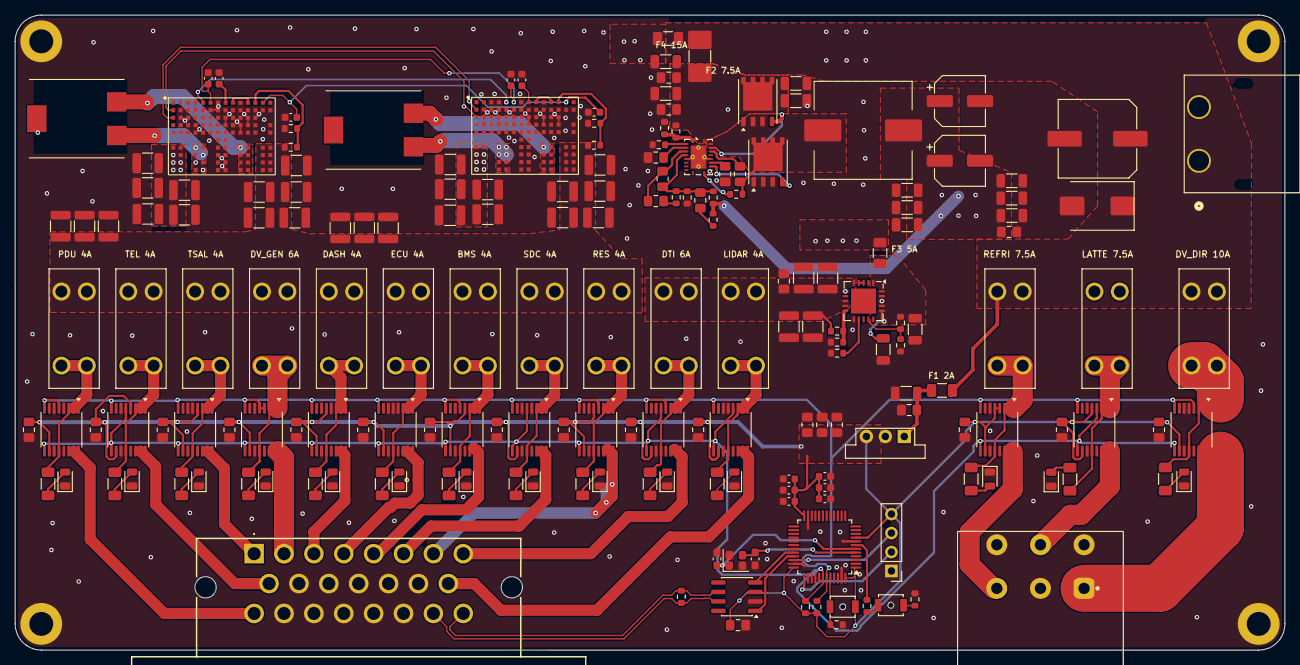
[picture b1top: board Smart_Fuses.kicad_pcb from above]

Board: 2 copper layers, 170.0 x 85.0 mm, 196 parts (0 on the bottom side), 98 nets.

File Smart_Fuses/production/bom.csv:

Designator,Footprint,Quantity,Value,LCSC Part #
"BMS1, DASH1, DTI1, DV_DIR1, DV_EBS1, DV_GENERAL1, ECU1, LATTEPANDA1, LIDAR1, PDU1, REFRI1, SDC1, TEL1, TSAL1",3568,14,3568,
"C1, C10, C11, C12, C13, C14, C2, C23, C3, C4, C5, C6, C7, C8, C9",0805,15,0.1u,
"C15, C16, C17",0603,3,100n,
C18,0603,1,4.7u,
C19,0603,1,10n,
C20,0603,1,1u,
"C25, C26, C39, C40, C41, C42, C44, C45, C46, C47, C48, C49, C55, C56",0805,14,10u,
"C27, C38, C43, C52, C54, C57",0805,6,100n,
"C28, C29, C30, C31, C58",0805,5,22u,
C32,0805,1,68n,
C33,0805,1,2.2u,
C34,0805,1,18p,
C35,0805,1,1.2n,
C36,0805,1,270p,
C50,0805,1,82u,
C51,0603,1,100u,
C53,0805,1,1u,
"C59, C60",0603,2,10p,
CR2,D_SMC,1,SMCJ33A,
F1,1206,1,Fuse 2A,
J1,776267-1,1,776267-1,
J2,PinHeader_1x04_P2.54mm_Vertical,1,Conn_01x04_Socket,
J3,Molex_Mega-Fit_76825-0004_2x02_P5.70mm_Horizontal,1,76825-0004,
J4,17760871,1,1-776087-1,
L1,L_Wuerth_WE-HCI-1050,1,10u,
"LED10, LED11, LED12, LED13, LED14, LED15, LED2, LED3, LED4, LED5, LED6, LED7, LED8, LED9",LED_LSM0805-2P0X1P25X0P8_VCC,14,LSM0805412V,
"R1, R13, R14, R15, R16, R17, R18, R19, R20, R21, R22",1206,11,4.7k,
R10,0603,1,27.4k,
R11,0603,1,110k,
"R12, R4, R40",0603,3,10k,
"R2, R3",0603,2,4.7k,
"R23, R24",1206,2,2.2k,
R25,1206,1,3.6k,
R26,0603,1,200k,
R27,0603,1,12.7k,
R28,0603,1,33.2k,
R29,0603,1,61.9k,
R30,0603,1,6.04k,
R31,0603,1,137k,
R32,0603,1,8.25k,
R33,0603,1,365,
R5,0603,1,33,
R8,0603,1,100k,
R9,0603,1,7.5k,
"SW1, SW2",SW_SPST_B3U-1000P-B,2,SW_Push,
"U1, U10, U11, U12, U13, U14, U2, U3, U4, U5, U6, U7, U8, U9",TSSOP-16_4.4x5mm_P0.65mm,14,INA260,
U15,Converter_DCDC_Murata_OKI-78SR_Vertical,1,OKI-78SR-3.3_1.5-W36-C,
U16,RGY0020B,1,LM5145RGYR,
"U17, U21",PowerPAK_SO-8_Single,2,CSD18534Q5A,
U18,RDL0020A-MFG,1,TPSM63606EXTRDLR,
U19,SOIC-8_3.9x4.9mm_P1.27mm,1,TCAN330,
U20,LQFP-48_7x7mm_P0.5mm,1,STM32L431CBTx,
Y2,Crystal_SMD_2520-4Pin_2.5x2.0mm,1,24MHz,
